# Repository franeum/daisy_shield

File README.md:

# daisy_shield

http://tinyurl.com/yltugymq
/home/neum/.var/app/org.kicad.KiCad/

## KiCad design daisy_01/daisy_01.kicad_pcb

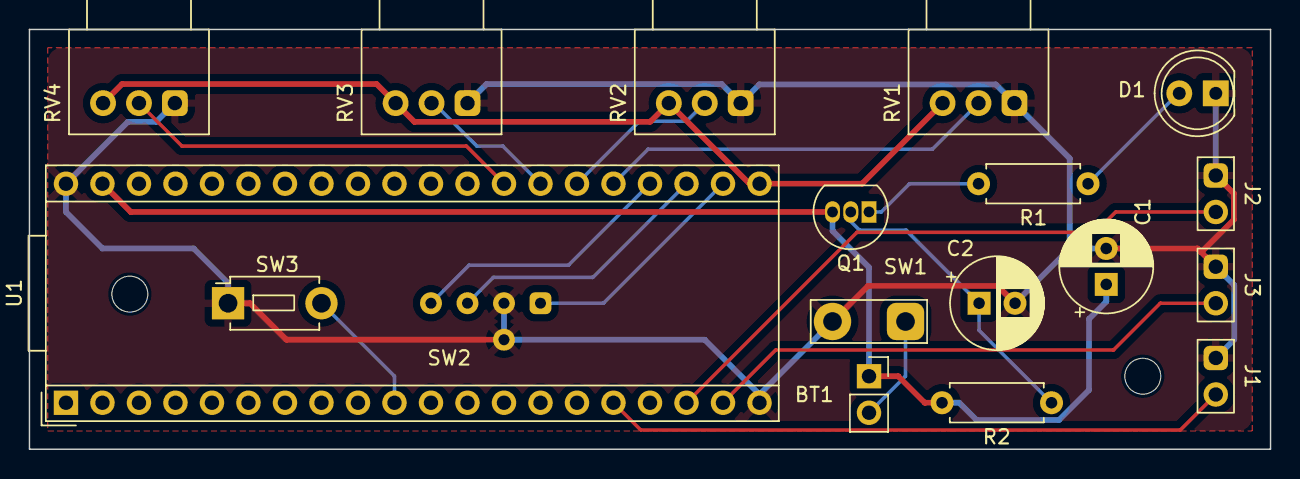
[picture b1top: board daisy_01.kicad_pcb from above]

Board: 2 copper layers, 86.4 x 29.2 mm, 20 parts (0 on the bottom side), 18 nets.

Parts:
BT1: Battery_Cell; PinSocket_1x02_P2.54mm_Vertical
C1: 220uF; CP_Radial_D6.3mm_P2.50mm
C2: 100uF; CP_Radial_D6.3mm_P2.50mm
D1: LED; LED_D5.0mm
J1: AudioInput; mono_jack
J2: AudioOutput1; mono_jack
J3: AudioOutput2; mono_jack
Q1: PN2222A; TO-92_Inline
R1: 470; R_Axial_DIN0207_L6.3mm_D2.5mm_P7.62mm_Horizontal
R2: 10K; R_Axial_DIN0207_L6.3mm_D2.5mm_P7.62mm_Horizontal
RV1, RV2, RV3, RV4: R_Potentiometer; Potentiometer_Alps_RK097_Single_Horizontal
SW1: SW_SPST; TestPoint_2Pads_Pitch5.08mm_Drill1.3mm
SW2: RotaryEncoder_Switch; ec11_encoder_mio
SW3: SW_Push; SW_PUSH_1P1T_6x3.5mm_H5.0_APEM_MJTP1250
U1: Device_Audio_Electrosmith_Daisy_Seed
screw1, screw2: MountingHole_2.5mm

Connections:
+9V: BT1.1 (+), C1.1, Q1.3 (C), R2.2, U1.39 (VIN)
/A_PWR3.3: RV1.3, RV2.3, RV3.3, RV4.3, U1.21 (3V3_ANALOG)
GND: C1.2, C2.2, D1.1 (K), J1.S, J2.S, J3.S, RV1.1, RV2.1, RV3.1, RV4.1, SW1.2 (B), SW2.C, SW2.S1, SW3.1, U1.20 (AGND), U1.40 (DGND)
unnamed: BT1.2 (-), SW1.1 (A)
unnamed: D1.2 (A), R1.1
unnamed: J1.T, U1.16 (Audio_In_1)
unnamed: C2.1, Q1.2 (B), R2.1
unnamed: Q1.1 (E), R1.2
unnamed: SW2.A, U1.22 (A0/D15)
unnamed: SW2.B, U1.23 (A1/D16)
unnamed: SW2.S2, U1.24 (A2/D17)
unnamed: RV1.2, U1.25 (A3/D18)
unnamed: RV2.2, U1.26 (A4/D19)
unnamed: RV3.2, U1.27 (A5/D20)
unnamed: RV4.2, U1.28 (A5/D21)
unnamed: J2.T, U1.18 (Audio_Out_1)
unnamed: J3.T, U1.19 (Audio_Out_2)
unnamed: SW3.2, U1.10 (D9)

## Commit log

2024-01-29 update gerber && drill
